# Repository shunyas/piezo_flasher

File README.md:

# piezo_flasher
Uchiwa
Attach a piezo element. It works as an input device as well as output device (speaker).

## pins

piezoPin = 3 (PD3)
pixelPin = 10 (PB2)
pixPWRPin = A1 (PC1)
modePins[] = {8, 6, 5, 21, 20};
Mode0 8 (PB0)
Mode1 6 (PD6)
Mode2 5 (PD5)
Mode3 21 (PB7)
Mode4 20 (PB6)

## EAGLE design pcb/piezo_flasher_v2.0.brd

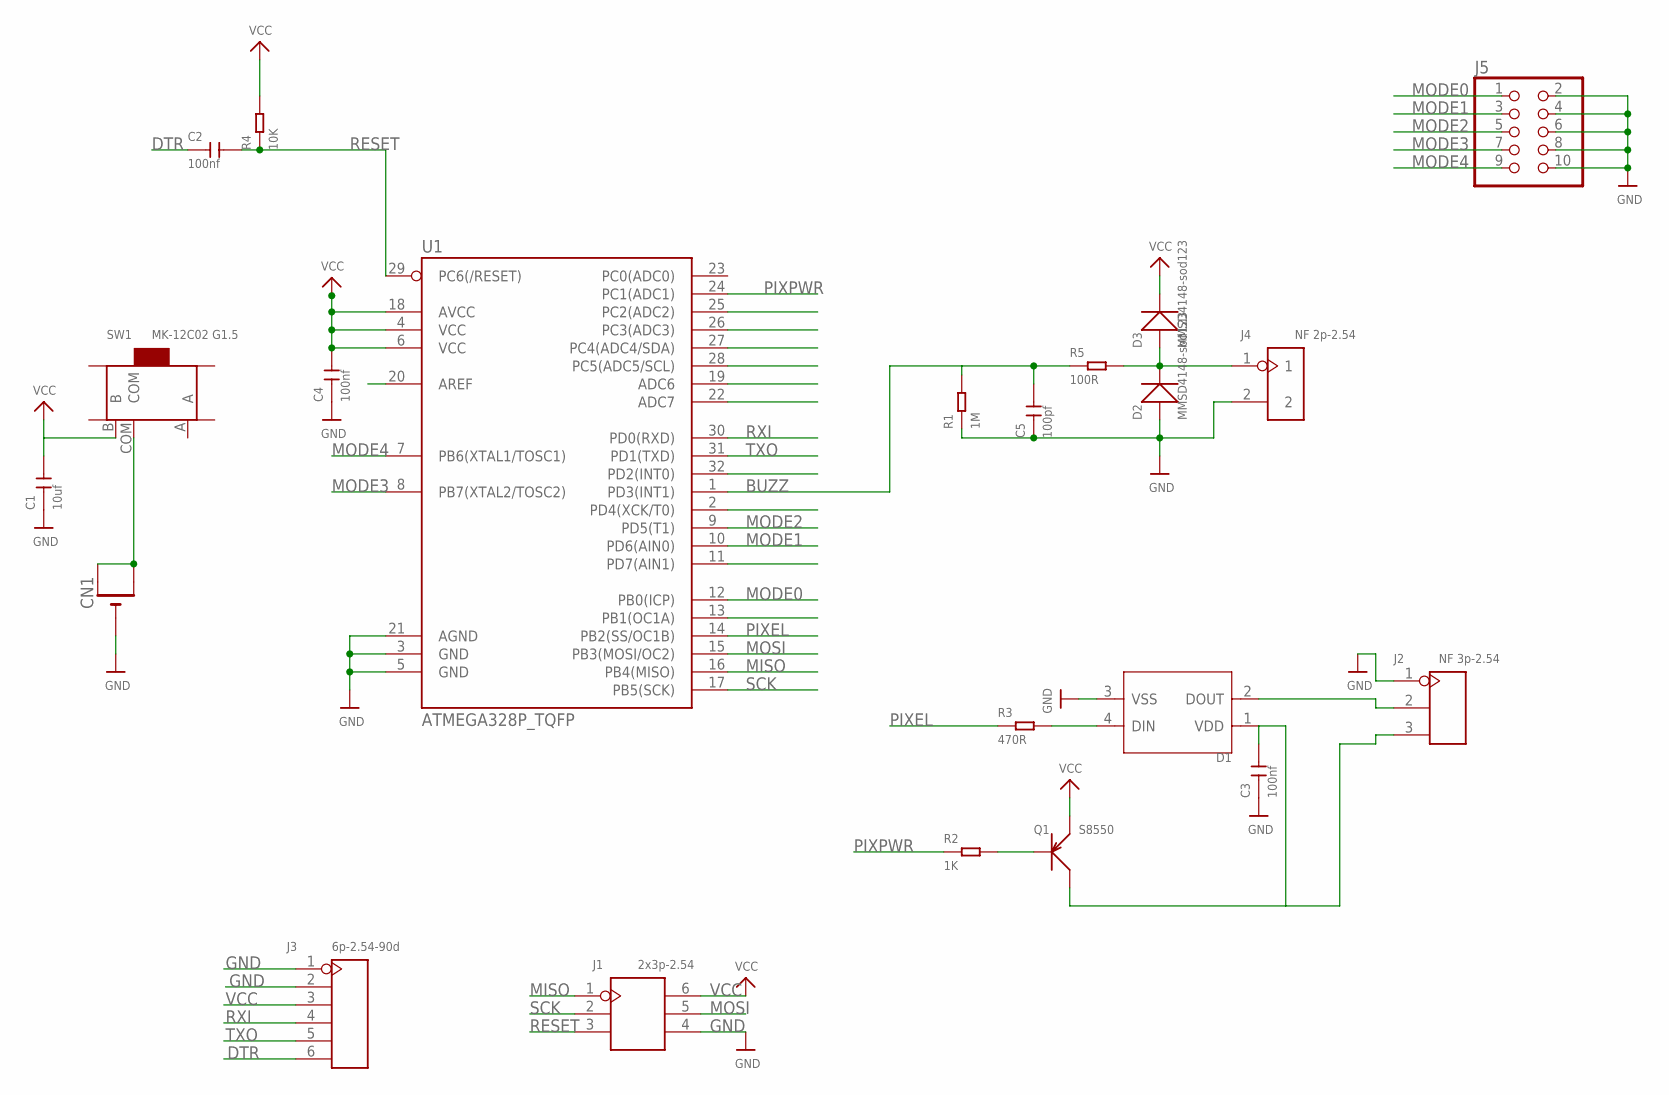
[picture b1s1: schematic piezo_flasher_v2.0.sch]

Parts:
C1: 10uf; C0805
C2, C3, C4: 100nf; C0805
C5: 100pf; C0603
CN1: CR2032SMT; CR2032-SMD
D1: SMD-RGB-LED-4P'WS2812B'; LED4-SMD-5050
D2, D3: MMSD4148-sod123; SOD-123
J1: 2x3p-2.54; H2X3-2.54
J2: NF 3p-2.54; H3-2.54
J3: 6p-2.54-90d; H6-2.54-90D-MALE
J4: NF 2p-2.54; H2-2.54
J5: HEADER-2X5; 2X05
Q1: S8550; SOT-23
R1: 1M; R0603
R2: 1K; R0805
R3: 470R; R0603
R4: 10K; R0805
R5: 100R; R0805
SW1: MK-12C02 G1.5; SW7-SMD-L6.7X2.7X3.2MM
U1: ATMEGA328P_TQFP; TQFP32-08

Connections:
BUZZ: C5.2, R1.2, R5.1, U1.1 (PD3(INT1))
DTR: C2.1, J3.6
GND: C1.1, C3.1, C4.1, C5.1, CN1.-, D1.3 (VSS), D2.+, J1.4, J2.1, J3.1, J3.2, J4.2, J5.2, J5.4, J5.6, J5.8, J5.10, R1.1, U1.3 (GND), U1.5 (GND), U1.21 (AGND)
MISO: J1.1, U1.16 (PB4(MISO))
MODE0: J5.1, U1.12 (PB0(ICP))
MODE1: J5.3, U1.10 (PD6(AIN0))
MODE2: J5.5, U1.9 (PD5(T1))
MODE3: J5.7, U1.8 (PB7(XTAL2/TOSC2))
MODE4: J5.9, U1.7 (PB6(XTAL1/TOSC1))
MOSI: J1.5, U1.15 (PB3(MOSI/OC2))
unnamed: Q1.1 (B), R2.2
unnamed: D1.4 (DIN), R3.2
unnamed: D2.-, D3.+, J4.1, R5.2
unnamed: D1.2 (DOUT), J2.2
unnamed: C3.2, D1.1 (VDD), J2.3, Q1.3 (C)
unnamed: CN1.+$1 (+), CN1.+$2 (+1), SW1.COM
PIXEL: R3.1, U1.14 (PB2(SS/OC1B))
PIXPWR: R2.1, U1.24 (PC1(ADC1))
RESET: C2.2, J1.3, R4.1, U1.29 (PC6(/RESET))
RXI: J3.4, U1.30 (PD0(RXD))
SCK: J1.2, U1.17 (PB5(SCK))
TXO: J3.5, U1.31 (PD1(TXD))
VCC: C1.2, C4.2, D3.-, J1.6, J3.3, Q1.2 (E), R4.2, SW1.B, U1.4 (VCC), U1.6 (VCC), U1.18 (AVCC)

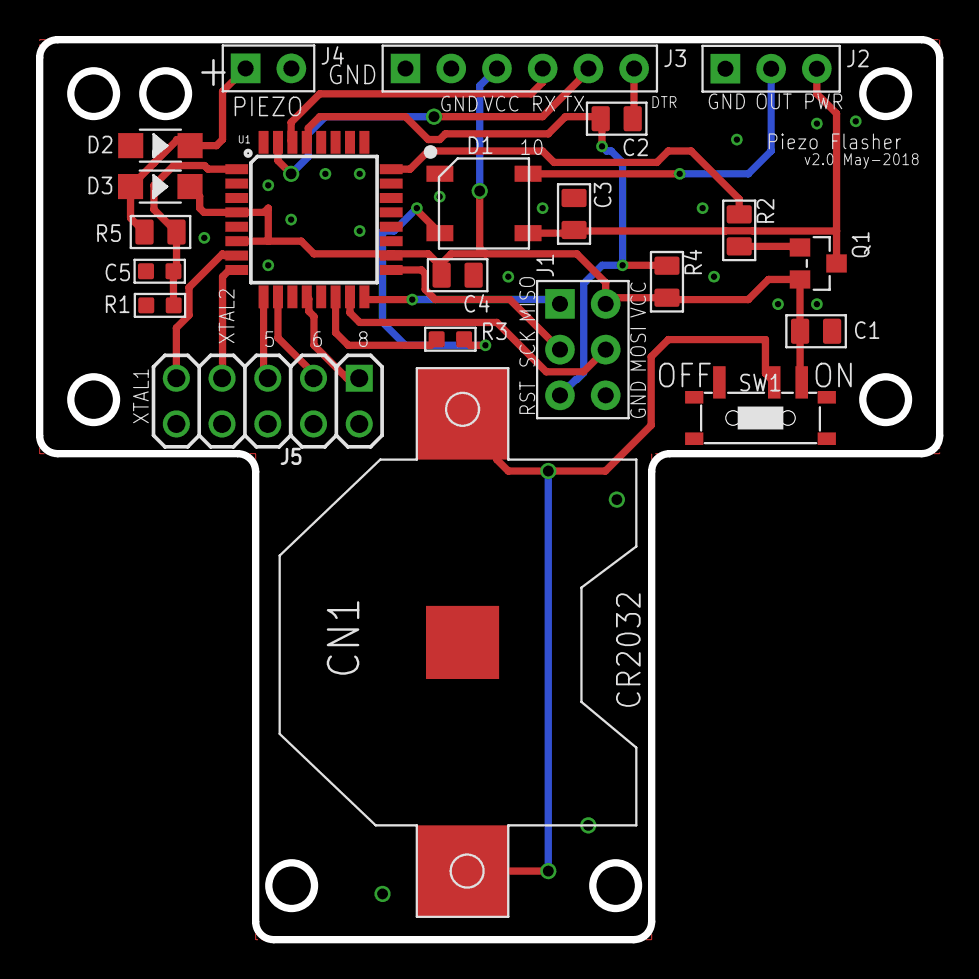
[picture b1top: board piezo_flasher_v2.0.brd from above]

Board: 2 copper layers, 50.0 x 50.0 mm, 22 parts (0 on the bottom side), 23 nets.

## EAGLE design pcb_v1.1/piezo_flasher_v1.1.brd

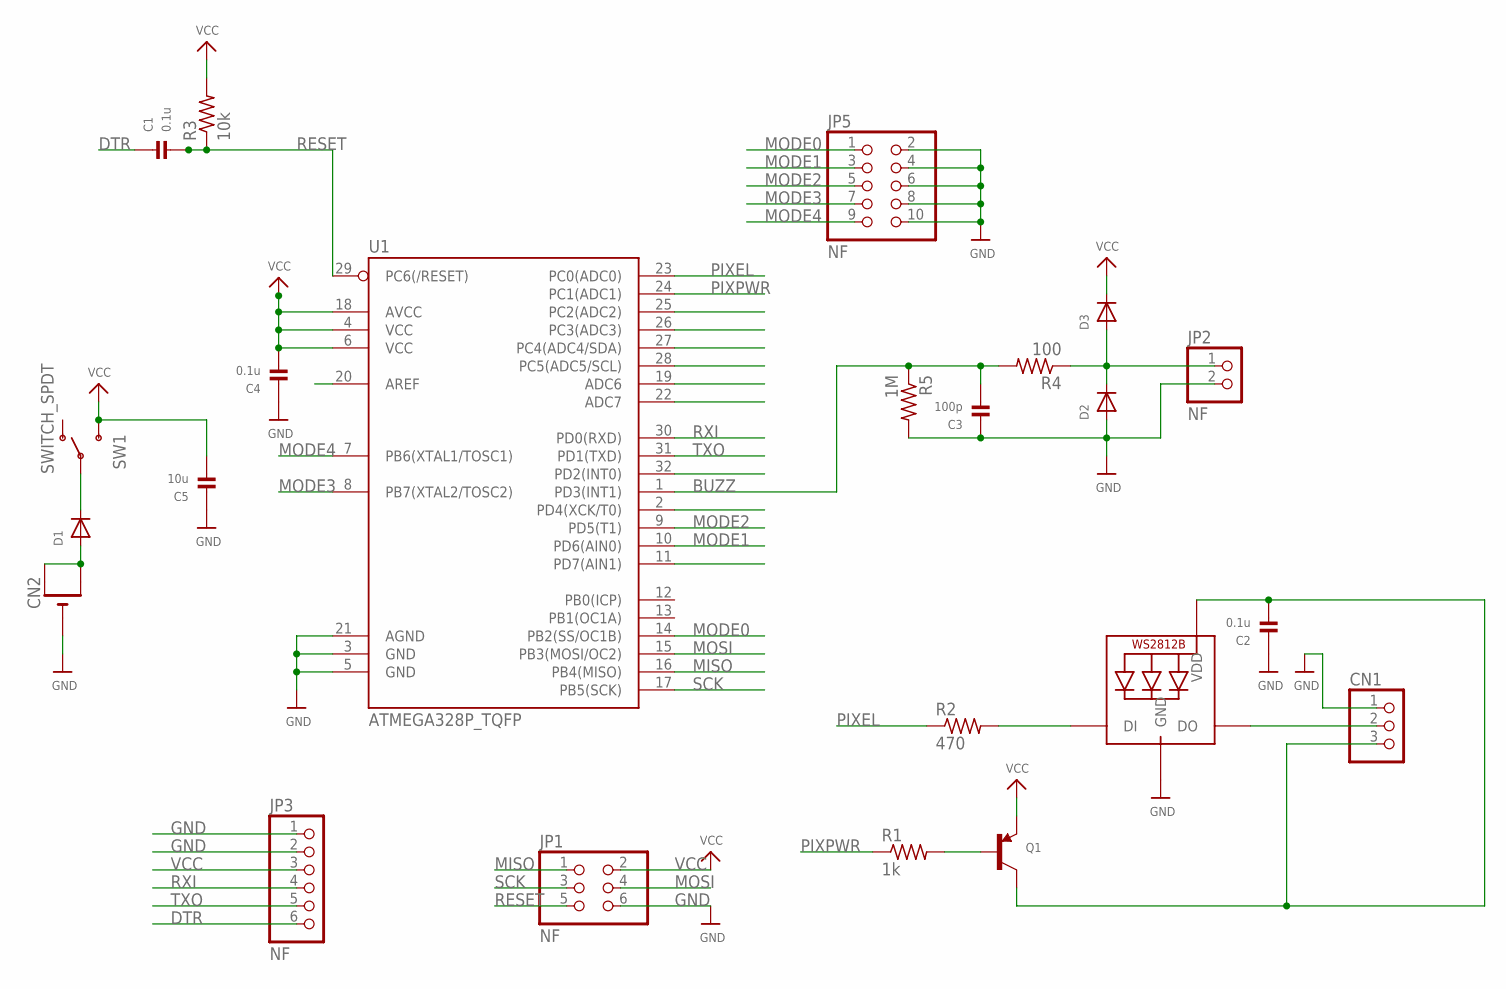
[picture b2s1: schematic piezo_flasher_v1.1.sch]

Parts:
C1, C2, C4: 0.1u; 0805
C3: 100p; 0805
C5: 10u; 0805
CN1: JST_3PIN; JSTPH3
CN2: CR2032SMT; CR2032-SMD
D1, D2, D3: DIODESOD-323; SOD-323
JP1: NF; 2X03_ROUND_70MIL
JP2: NF; 1X02_ROUND
JP3: NF; 1X06_ROUND
JP5: NF; 2X05
LED1: WS2812B5050; WS2812B
Q1: TRANSISTOR_PNPWIDE; SOT23-WIDE
R1: 1k; R0805
R2: 470; R0805
R3: 10k; R0805
R4: 100; R0805
R5: 1M; R0805
SW1: SWITCH_SPDT; KPS-1290
U1: ATMEGA328P_TQFP; TQFP32-08

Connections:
BUZZ: C3.2, R4.2, R5.1, U1.1 (PD3(INT1))
DTR: C1.1, JP3.6
GND: C2.1, C3.1, C4.1, C5.1, CN1.1, CN2.-, D2.A, JP1.6, JP2.2, JP3.1, JP3.2, JP5.2, JP5.4, JP5.6, JP5.8, JP5.10, LED1.3-GND (GND), R5.2, U1.3 (GND), U1.5 (GND), U1.21 (AGND)
MISO: JP1.1, U1.16 (PB4(MISO))
MODE0: JP5.1, U1.14 (PB2(SS/OC1B))
MODE1: JP5.3, U1.10 (PD6(AIN0))
MODE2: JP5.5, U1.9 (PD5(T1))
MODE3: JP5.7, U1.8 (PB7(XTAL2/TOSC2))
MODE4: JP5.9, U1.7 (PB6(XTAL1/TOSC1))
MOSI: JP1.4, U1.15 (PB3(MOSI/OC2))
unnamed: Q1.1 (B), R1.2
unnamed: C2.2, CN1.3, LED1.1-VDD (VDD), Q1.3 (C)
unnamed: LED1.4-DIN (DI), R2.2
unnamed: D2.C, D3.A, JP2.1, R4.1
unnamed: CN1.2, LED1.2-DOUT (DO)
unnamed: CN2.+$1 (+), CN2.+$2 (+1), D1.A
unnamed: D1.C, SW1.P
PIXEL: R2.1, U1.23 (PC0(ADC0))
PIXPWR: R1.1, U1.24 (PC1(ADC1))
RESET: C1.2, JP1.5, R3.1, U1.29 (PC6(/RESET))
RXI: JP3.4, U1.30 (PD0(RXD))
SCK: JP1.3, U1.17 (PB5(SCK))
TXO: JP3.5, U1.31 (PD1(TXD))
VCC: C4.2, C5.2, D3.C, JP1.2, JP3.3, Q1.2 (E), R3.2, SW1.S, U1.4 (VCC), U1.6 (VCC), U1.18 (AVCC)

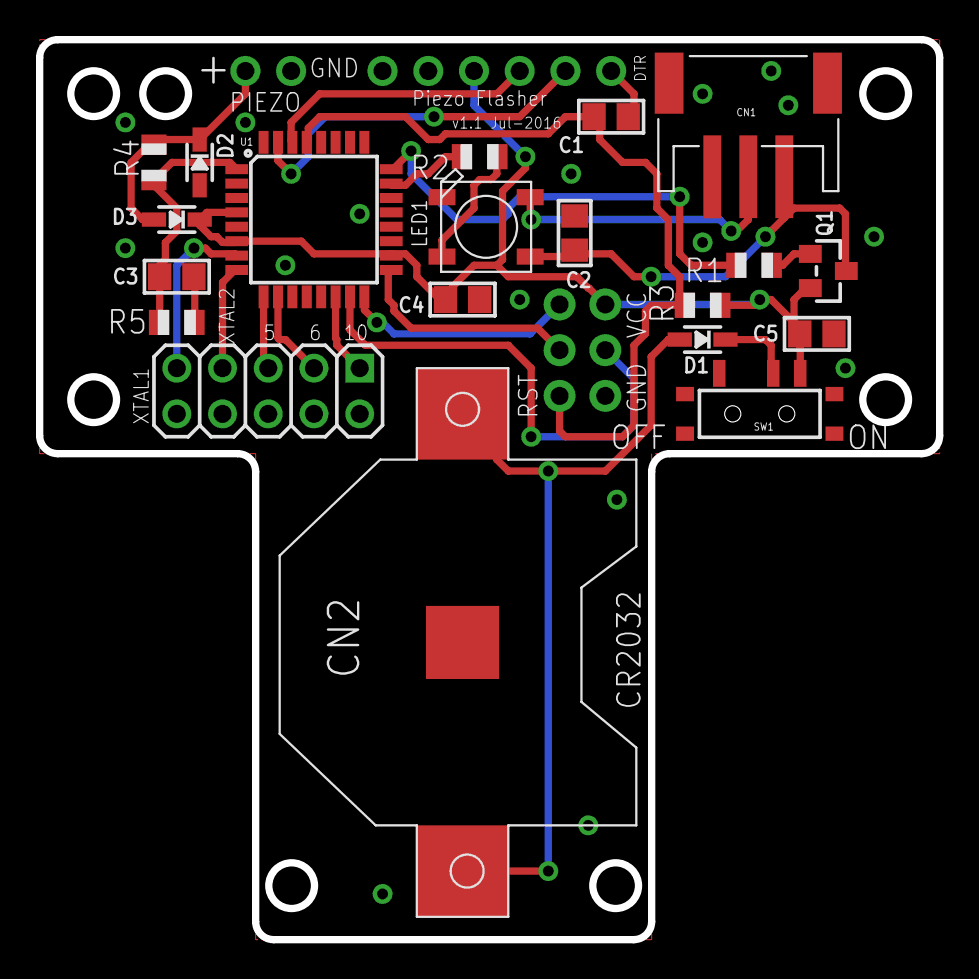
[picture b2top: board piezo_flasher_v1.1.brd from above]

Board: 2 copper layers, 50.0 x 50.0 mm, 23 parts (1 on the bottom side), 24 nets.

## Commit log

2016-08-16 for v1.1 release
2018-07-24 Move pcb_v1.1
2018-07-24 Add pcb v2.0 files
2018-07-29 Add schematics and layout pdf and png

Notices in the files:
parts and their libraries:
microbuilder: This work is placed in the public domain, and may be freely used for commercial and non-commercial work with the following conditions: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
SparkFun-DigitalIC: Licensing: Creative Commons ShareAlike 4.0 International - https://creativecommons.org/licenses/by-sa/4.0
